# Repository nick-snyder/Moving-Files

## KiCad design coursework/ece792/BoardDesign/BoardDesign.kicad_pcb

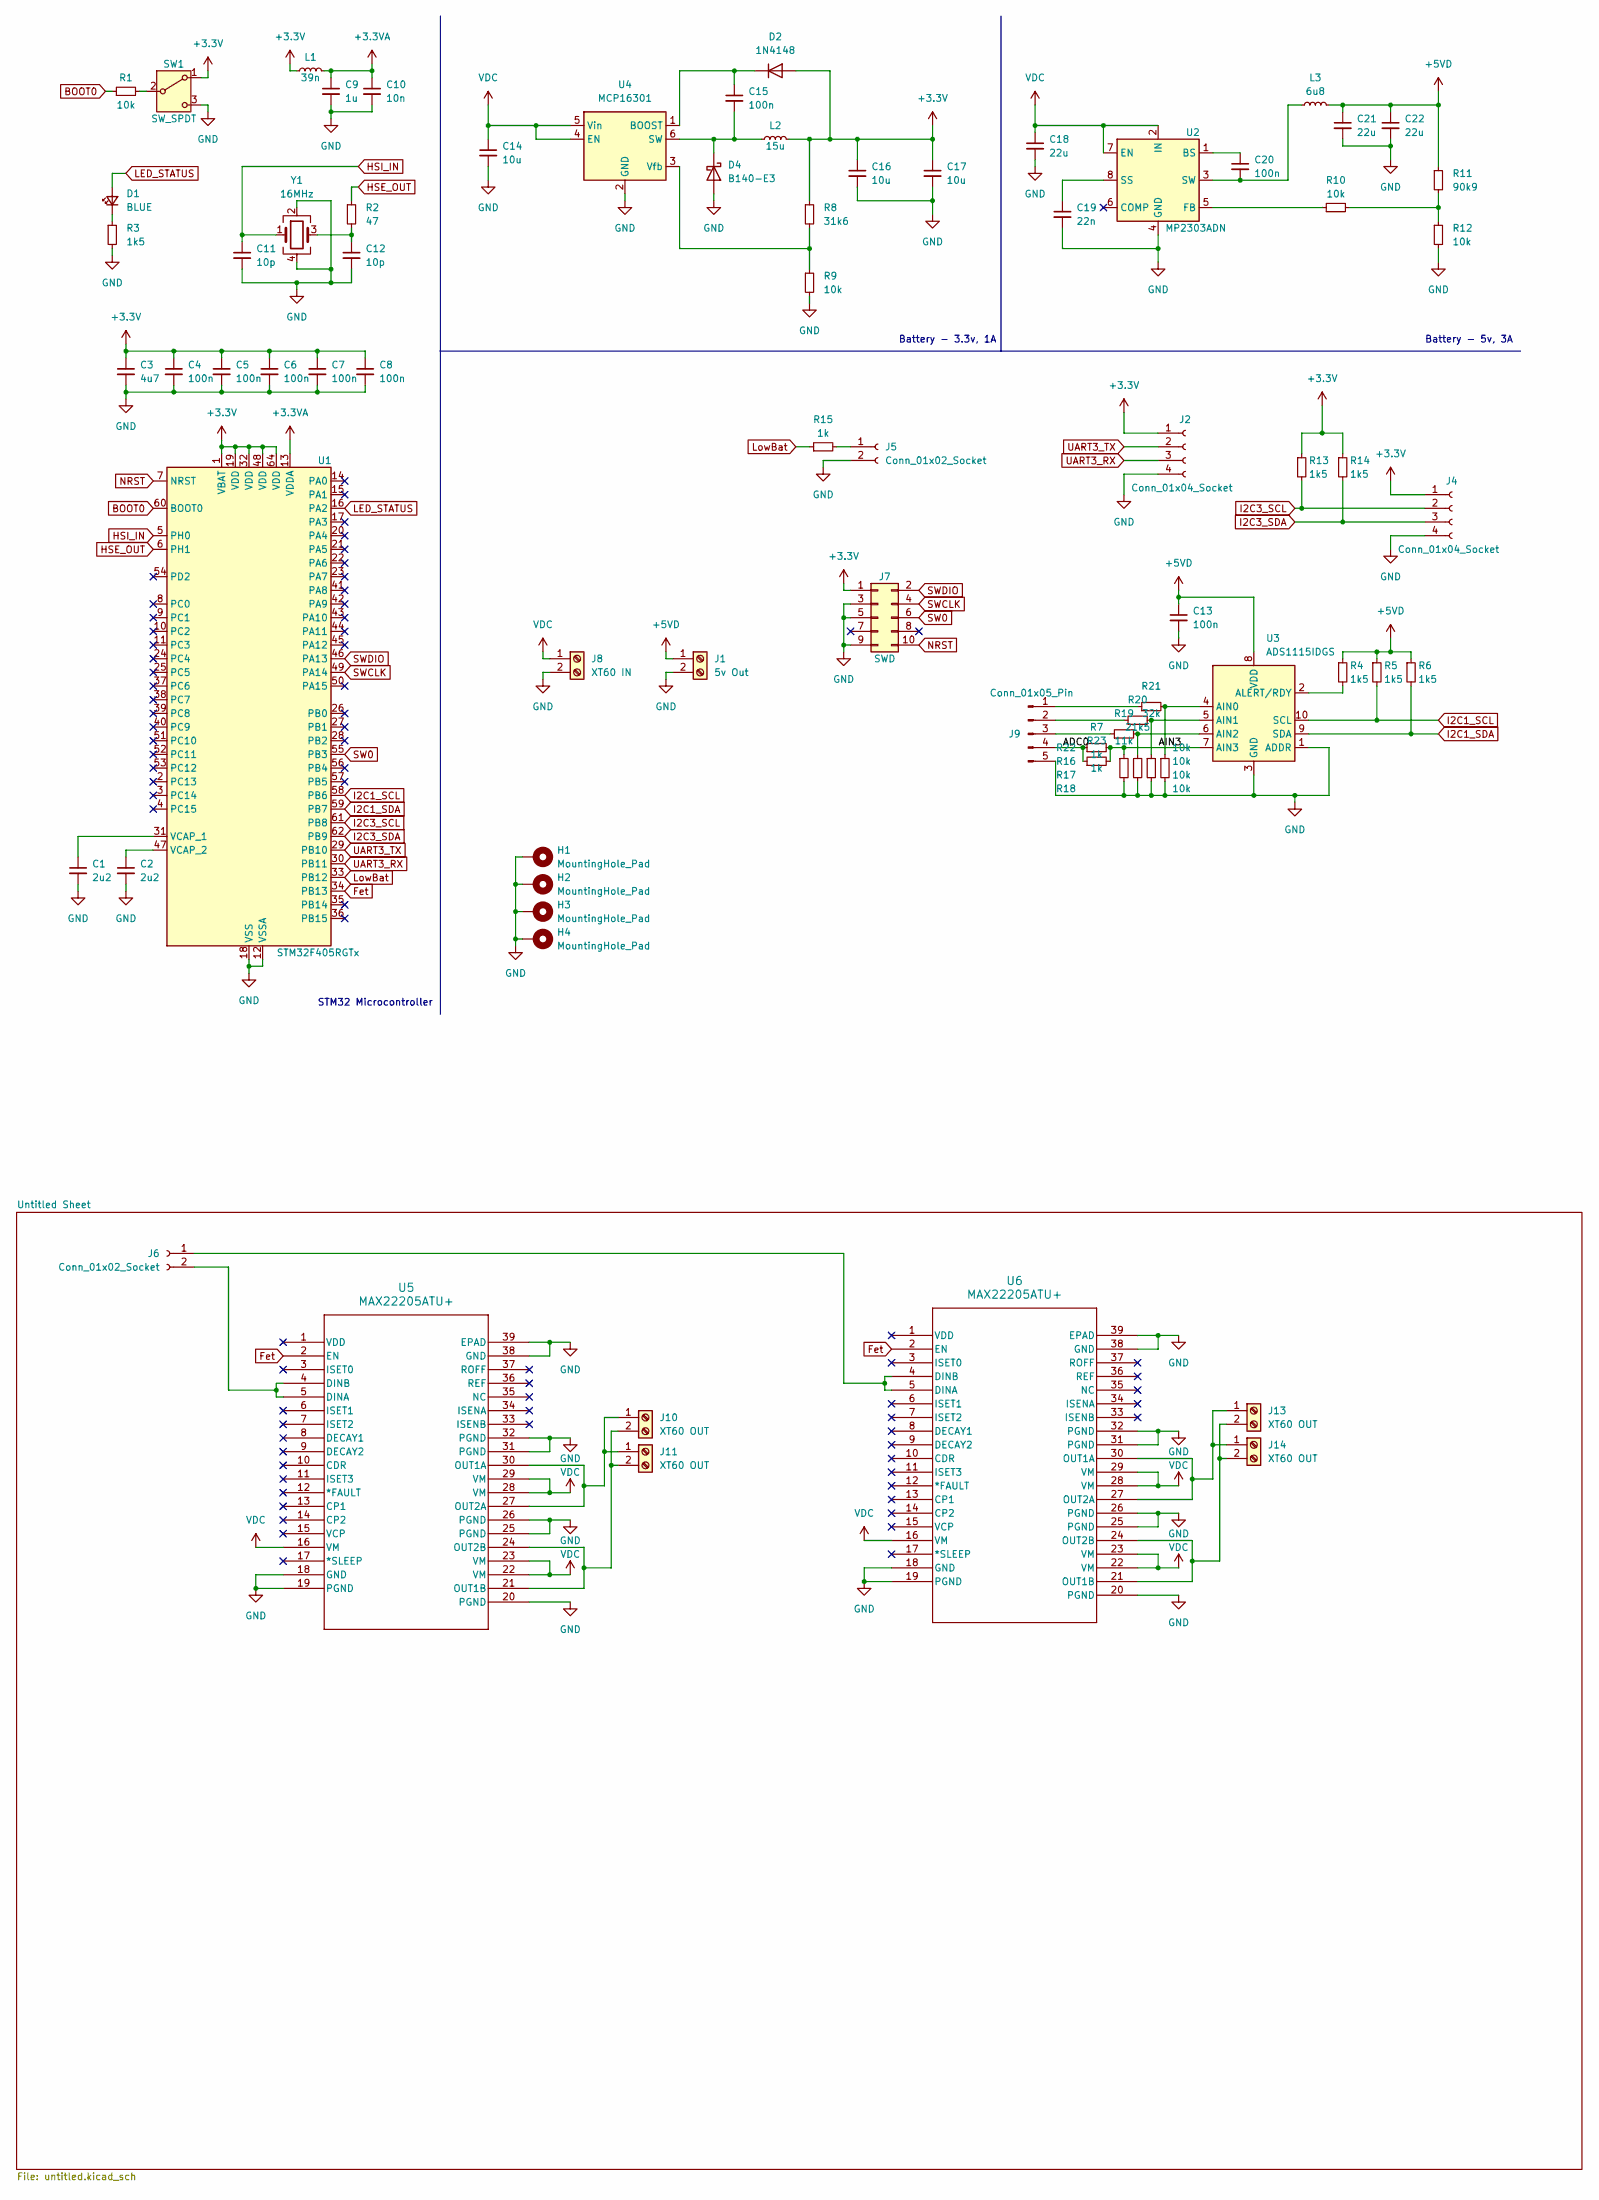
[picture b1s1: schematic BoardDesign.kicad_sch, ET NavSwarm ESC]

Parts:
C1, C2: 2u2; C_0603_1608Metric; LCSC Part # C23630
C3: 4u7; C_0603_1608Metric; LCSC Part # C19666
C4, C5, C6, C7, C8, C13, C15, C20: 100n; C_0402_1005Metric; LCSC Part # C307331
C9: 1u; C_0402_1005Metric; LCSC Part # C52923
C10: 10n; C_0402_1005Metric; LCSC Part # C15195
C11, C12: 10p; C_0402_1005Metric; LCSC Part # C32949
C14, C16, C17: 10u; C_1206_3216Metric; LCSC Part # C13585
C18, C21, C22: 22u; C_1206_3216Metric; LCSC Part # C12891
C19: 22n; C_0402_1005Metric; LCSC Part # C1532
D1: BLUE; LED_0603_1608Metric; LCSC Part # C2286
D2: 1N4148; D_DO-35_SOD27_P7.62mm_Horizontal; LCSC Part # C81598
D4: B140-E3; D_SMA; LCSC Part # C142601
H1, H2, H3, H4: MountingHole_Pad; MountingHole_4.3mm_M4_Pad_Via
J1: 5v Out; PinHeader_1x02_P2.54mm_Vertical
J2, J4: Conn_01x04_Socket; PinHeader_1x04_P2.54mm_Vertical
J5, J6: Conn_01x02_Socket; PinHeader_1x02_P2.54mm_Vertical
J7: SWD; PinHeader_2x05_P1.27mm_Vertical
J8: XT60 IN; AMASS_XT60-M_1x02_P7.20mm_Vertical
J9: Conn_01x05_Pin; JST_XH_B5B-XH-A_1x05_P2.50mm_Vertical
J10, J11, J13, J14: XT60 OUT; AMASS_XT60-F_1x02_P7.20mm_Vertical
L1: 39n; L_0402_1005Metric; LCSC Part # C275324
L2: 15u; L_Sunlord_MWSA0603S; LCSC Part # C408452
L3: 6u8; L_Sunlord_SWPA6045S; LCSC Part # C57254
R1, R9, R10, R12, R16, R17, R18, R22: 10k; R_0603_1608Metric; LCSC Part # C25804
R2: 47; R_0402_1005Metric; LCSC Part # C25792
R3, R4, R5, R6, R13, R14: 1k5; R_0603_1608Metric; LCSC Part # C22843
R7, R15, R23: 1k; R_0603_1608Metric; LCSC Part # C21190
R8: 31k6; R_0603_1608Metric; LCSC Part # C3016363
R11: 90k9; R_0603_1608Metric; LCSC Part # C728600
R19: 11k; R_0603_1608Metric; LCSC Part # C100720
R20: 21k5; R_0603_1608Metric; LCSC Part # C303835
R21: 32k; R_0603_1608Metric; LCSC Part # C1613
SW1: SW_SPDT; SW_SPDT_PCM12
U1: STM32F405RGTx; LQFP-64_10x10mm_P0.5mm; LCSC Part # C15742
U2: MP2303ADN; SOIC-8-1EP_3.9x4.9mm_P1.27mm_EP2.62x3.51mm; LCSC Part # C18876
U3: ADS1115IDGS; TSSOP-10_3x3mm_P0.5mm; LCSC Part # C37593
U4: MCP16301; SOT-23-6; LCSC Part # C511272
U5, U6: MAX22205ATU+; 21-0172_T3857-1C_MXM; LCSC Part # C3681230
Y1: 16MHz; Crystal_SMD_3225-4Pin_3.2x2.5mm; LCSC Part # C13738

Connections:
+3.3V: C3.1, C4.1, C5.1, C6.1, C7.1, C8.1, C16.1, C17.1, D2.2 (A), J2.1, J4.1, J7.1, L1.1, L2.2, R8.1, R13.1, R14.1, SW1.1 (A), U1.1 (VBAT), U1.19 (VDD), U1.32 (VDD), U1.48 (VDD), U1.64 (VDD)
+3.3VA: C9.1, C10.1, L1.2, U1.13 (VDDA)
+5VD: C13.1, C21.1, C22.1, J1.1, L3.2, R4.1, R5.1, R6.1, R11.1, U3.8 (VDD)
/ADC0: J9.4, R7.1, R23.1
/AIN3: R7.2, R22.1, R23.2, U3.7 (AIN3)
BOOT0: R1.1, U1.60 (BOOT0)
Fet: U1.34 (PB13), U5.2 (EN), U6.2 (EN)
GND: C1.2, C2.2, C3.2, C4.2, C5.2, C6.2, C7.2, C8.2, C9.2, C10.2, C11.2, C12.2, C13.2, C14.2, C16.2, C17.2, C18.2, C19.2, C21.2, C22.2, D4.2 (A), H1.1, H2.1, H3.1, H4.1, J1.2, J2.4, J4.4, J5.2, J7.3, J7.5, J7.9, J8.2, J9.5, R3.2, R9.2, R12.2, R16.2, R17.2, R18.2, R22.2, SW1.3 (C), U1.12 (VSSA), U1.18 (VSS), U1.63 (VSS), U2.4 (GND), U3.1 (ADDR), U3.3 (GND), U4.2 (GND), U5.18 (GND), U5.19 (PGND), U5.20 (PGND), U5.25 (PGND), U5.26 (PGND), U5.31 (PGND), U5.32 (PGND), U5.38 (GND), U5.39 (EPAD), U6.18 (GND), U6.19 (PGND), U6.20 (PGND), U6.25 (PGND), U6.26 (PGND), U6.31 (PGND), U6.32 (PGND), U6.38 (GND), U6.39 (EPAD), Y1.2, Y1.4
HSE_OUT: R2.1, U1.6 (PH1)
HSI_IN: C11.1, U1.5 (PH0), Y1.1
I2C1_SCL: R5.2, U1.58 (PB6), U3.10 (SCL)
I2C1_SDA: R6.2, U1.59 (PB7), U3.9 (SDA)
I2C3_SCL: J4.2, R13.2, U1.61 (PB8)
I2C3_SDA: J4.3, R14.2, U1.62 (PB9)
LED_STATUS: D1.2 (A), U1.16 (PA2)
LowBat: R15.1, U1.33 (PB12)
NRST: J7.10, U1.7 (NRST)
unnamed: C12.1, R2.2, Y1.3
unnamed: D1.1 (K), R3.1
unnamed: C15.1, D2.1 (K), U4.1 (BOOST)
unnamed: C15.2, D4.1 (K), L2.1, U4.6 (SW)
unnamed: J5.1, R15.2
unnamed: J6.1, U6.4 (DINB), U6.5 (DINA)
unnamed: J6.2, U5.4 (DINB), U5.5 (DINA)
unnamed: J9.1, R21.1
unnamed: J9.2, R20.1
unnamed: J9.3, R19.1
unnamed: J10.1, J11.1, U5.27 (OUT2A), U5.30 (OUT1A)
unnamed: J10.2, J11.2, U5.21 (OUT1B), U5.24 (OUT2B)
unnamed: J13.1, J14.1, U6.27 (OUT2A), U6.30 (OUT1A)
unnamed: J13.2, J14.2, U6.21 (OUT1B), U6.24 (OUT2B)
unnamed: R10.2, R11.2, R12.1
unnamed: R1.2, SW1.2 (B)
unnamed: C1.1, U1.31 (VCAP_1)
unnamed: C2.1, U1.47 (VCAP_2)
unnamed: C20.1, U2.1 (BS)
unnamed: R10.1, U2.5 (FB)
unnamed: C19.1, U2.8 (SS)
unnamed: C20.2, L3.1, U2.3 (SW)
unnamed: R18.1, R21.2, U3.4 (AIN0)
unnamed: R17.1, R20.2, U3.5 (AIN1)
unnamed: R16.1, R19.2, U3.6 (AIN2)
unnamed: R4.2, U3.2 (ALERT/RDY)
unnamed: R8.2, R9.1, U4.3 (Vfb)
SW0: J7.6, U1.55 (PB3)
SWCLK: J7.4, U1.49 (PA14)
SWDIO: J7.2, U1.46 (PA13)
UART3_RX: J2.3, U1.30 (PB11)
UART3_TX: J2.2, U1.29 (PB10)
VDC: C14.1, C18.1, J8.1, U2.2 (IN), U2.7 (EN), U4.4 (EN), U4.5 (Vin), U5.16 (VM), U5.22 (VM), U5.23 (VM), U5.28 (VM), U5.29 (VM), U6.16 (VM), U6.22 (VM), U6.23 (VM), U6.28 (VM), U6.29 (VM)

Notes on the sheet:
STM32 Microcontroller
Battery - 5v, 3A
Battery - 3.3v, 1A

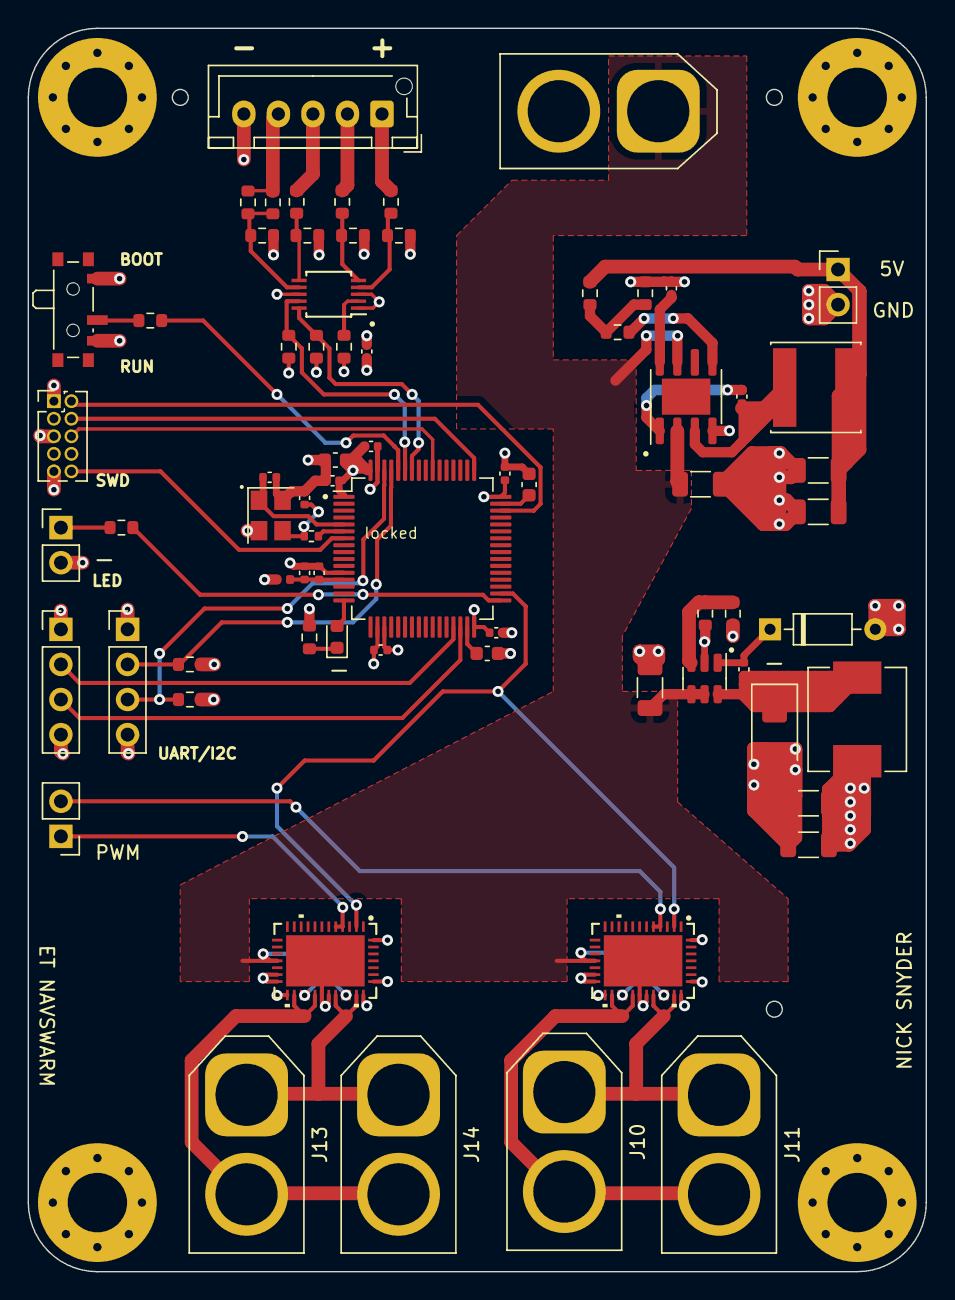
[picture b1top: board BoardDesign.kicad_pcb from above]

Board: 4 copper layers, 65.0 x 90.0 mm, 75 parts (0 on the bottom side), 50 nets.

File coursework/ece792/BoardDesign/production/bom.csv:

Designator,Footprint,Quantity,Value,LCSC Part #
"C1, C2",0603,2,2u2,
C10,0402,1,10n,
"C11, C12",0402,2,10p,
"C13, C15, C20, C4, C5, C6, C7, C8",0402,8,100n,
"C14, C16, C17",1206,3,10u,
"C18, C21, C22",1206,3,22u,
C19,0402,1,22n,
C3,0603,1,4u7,
C9,0402,1,1u,
D1,0603,1,BLUE,
D2,D_DO-35_SOD27_P7.62mm_Horizontal,1,1N4148,
D4,D_SMA,1,B140-E3,
"H1, H2, H4",MountingHole_4.3mm_M4_Pad_Via,3,MountingHole_Pad,
H3,MountingHole_4.3mm_M4_Pad_Via,1,MountingHole_Pad,
J1,PinHeader_1x02_P2.54mm_Vertical,1,5v Out,
"J10, J11, J13, J14",AMASS_XT60-F_1x02_P7.20mm_Vertical,4,XT60 OUT,
"J2, J4",PinHeader_1x04_P2.54mm_Vertical,2,Conn_01x04_Socket,
"J5, J6",PinHeader_1x02_P2.54mm_Vertical,2,Conn_01x02_Socket,
J7,PinHeader_2x05_P1.27mm_Vertical,1,SWD,
J8,AMASS_XT60-M_1x02_P7.20mm_Vertical,1,XT60 IN,
J9,JST_XH_B5B-XH-AM_1x05_P2.50mm_Vertical,1,Conn_01x05_Pin,
L1,0402,1,39n,
L2,L_Sunlord_MWSA0603S,1,15u,C340242
L3,L_Sunlord_SWPA6045S,1,6u8,C334250
"R1, R10, R12, R16, R17, R18, R9",0603,7,10k,
R11,0603,1,90k9,
"R13, R14, R3, R4, R5, R6",0603,6,1k5,
R15,0603,1,500,
R19,0603,1,11k,
R2,0402,1,47,
R20,0603,1,21k5,
R21,0603,1,32k,
R22,0603,1,10k,C25804
"R23, R7",0603,2,1k,C21190
R8,0603,1,31k6,
SW1,SW_SPDT_PCM12,1,SW_SPDT,
U1,LQFP-64_10x10mm_P0.5mm,1,STM32F405RGTx,
U2,SOIC-8-1EP_3.9x4.9mm_P1.27mm_EP2.62x3.51mm,1,MP2303ADN,
U3,TSSOP-10_3x3mm_P0.5mm,1,ADS1115IDGS,C37593
U4,SOT-23-6,1,MCP16301,
"U5, U6",21-0172_T3857-1C_MXM,2,MAX22205ATU+,
Y1,Crystal_SMD_3225-4Pin_3.2x2.5mm,1,16MHz,

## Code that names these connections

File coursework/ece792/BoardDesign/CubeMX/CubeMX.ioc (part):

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Mcu.Name=STM32F405RGTx
Mcu.Package=LQFP64
Mcu.UserName=STM32F405RGTx
PA11.Mode=Device_Only
PA11.Signal=USB_OTG_FS_DM
PA12.Mode=Device_Only
PA12.Signal=USB_OTG_FS_DP
PA8.Mode=I2C
PA8.Signal=I2C3_SCL
PB12.Signal=GPIO_Output
PB13.Signal=GPIO_Output
PB6.Mode=I2C
PB6.Signal=I2C1_SCL
PB7.Mode=I2C
PB7.Signal=I2C1_SDA
PC10.Mode=Asynchronous
PC10.Signal=USART3_TX
PC11.Mode=Asynchronous
PC11.Signal=USART3_RX
PC9.Mode=I2C
PC9.Signal=I2C3_SDA
PH0-OSC_IN.Mode=HSE-External-Oscillator
PH0-OSC_IN.Signal=RCC_OSC_IN
PH1-OSC_OUT.Mode=HSE-External-Oscillator
PH1-OSC_OUT.Signal=RCC_OSC_OUT
RCC.HSE_VALUE=25000000
RCC.SYSCLKFreq_VALUE=16000000
board=custom

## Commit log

2025-01-22 Added files
2025-01-22 Update1
2025-01-23 Update 2
